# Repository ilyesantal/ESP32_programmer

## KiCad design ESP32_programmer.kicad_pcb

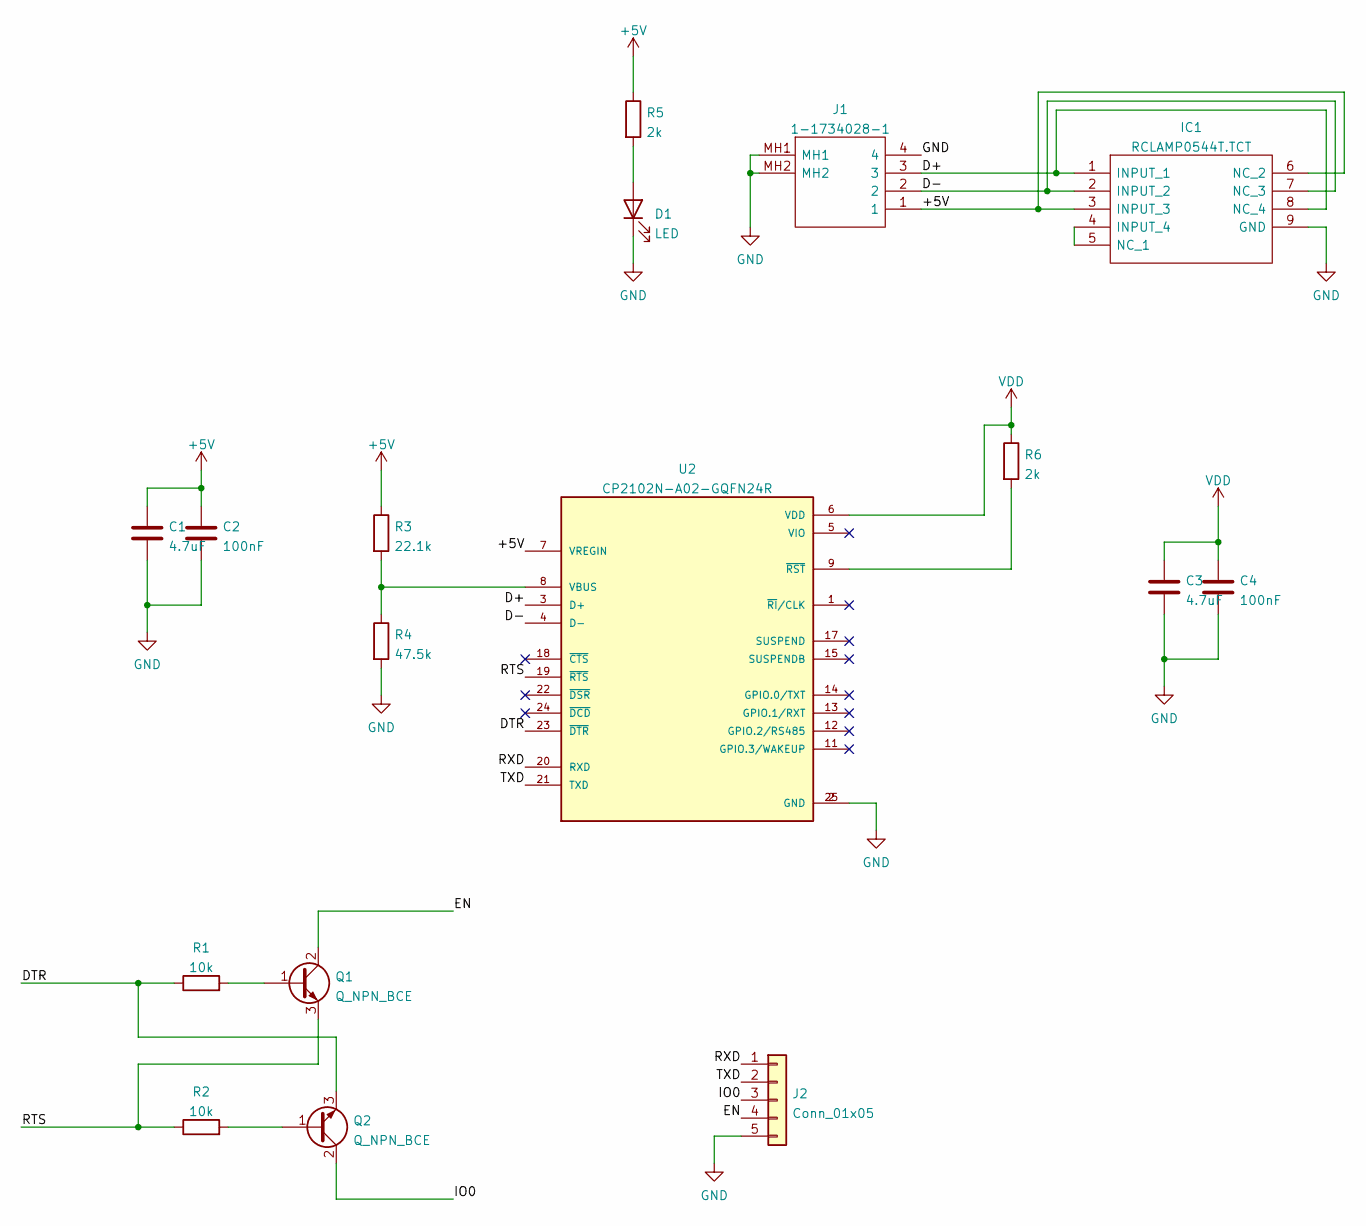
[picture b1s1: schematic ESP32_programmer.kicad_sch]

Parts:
C1, C3: 4.7uF; C_1206_3216Metric
C2, C4: 100nF; C_1206_3216Metric
D1: LED; LED_1206_3216Metric
IC1: RCLAMP0544T.TCT; RCLAMP0544TTCT; Mouser Part Number 947-RCLAMP0544T.TCT
J1: 1-1734028-1; USB_plug; Mouser Part Number 571-1-1734028-1
J2: Conn_01x05; PinHeader_1x05_P2.54mm_Vertical
Q1, Q2: Q_NPN_BCE; SOT-23
R1, R2: 10k; R_1206_3216Metric
R3: 22.1k; R_1206_3216Metric
R4: 47.5k; R_1206_3216Metric
R5, R6: 2k; R_1206_3216Metric
U2: CP2102N-A02-GQFN24R; PARTREV 1.3

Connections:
+5V: C1.1, C2.1, IC1.3 (INPUT_3), IC1.6 (NC_2), J1.1, R3.1, R5.1, U2.7 (VREGIN)
/D+: IC1.1 (INPUT_1), IC1.8 (NC_4), J1.3, U2.3 (D+)
/D-: IC1.2 (INPUT_2), IC1.7 (NC_3), J1.2, U2.4 (D-)
/DTR: Q2.3 (E), R1.1, U2.23 (~DTR)
/EN: J2.4, Q1.2 (C)
/IO0: J2.3, Q2.2 (C)
/RTS: Q1.3 (E), R2.1, U2.19 (~RTS)
/RXD: J2.1, U2.20 (RXD)
/TXD: J2.2, U2.21 (TXD)
GND: C1.2, C2.2, C3.2, C4.2, D1.1 (K), IC1.9 (GND), J1.4, J1.MH1, J1.MH2, J2.5, R4.2, U2.2 (GND), U2.25 (GND)
unnamed: D1.2 (A), R5.2
unnamed: IC1.4 (INPUT_4), IC1.5 (NC_1)
unnamed: Q1.1 (B), R1.2
unnamed: Q2.1 (B), R2.2
unnamed: R3.2, R4.1, U2.8 (VBUS)
unnamed: R6.2, U2.9 (~RST)
VDD: C3.1, C4.1, R6.1, U2.6 (VDD)

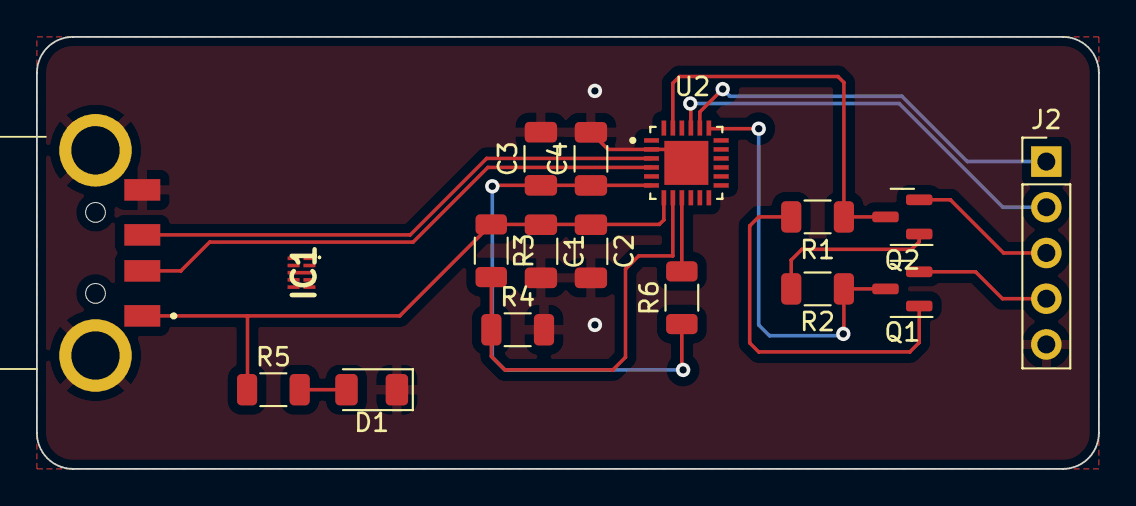
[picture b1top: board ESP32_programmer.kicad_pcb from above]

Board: 2 copper layers, 59.0 x 24.0 mm, 17 parts (0 on the bottom side), 17 nets.

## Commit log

2022-01-10 finished routing, diode must be solved
